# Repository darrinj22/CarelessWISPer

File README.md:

# CarelessWISPer 
Wireless Electronic Shopping Label | 
NCSU Senior Capstone Project 2021

## Introduction
CarelessWISPer, named after the famous (infamous?) George Michael song, is an Electronic Shopping Label System. Engineered
to act as an RFID area reader for consumer products, item tracking, and further applications. Using an ePaper Display, and ESP32 microcontroller, and an RFID module, this product has the capability of giving detailed item descriptions of each product on a shelf. 

## How to Browse

- This github repository is split into 3 main sections: Code, Tutorials, and Fabrication Files
- Within the code section, all of the code that was used to make this project work can be found. Note that this requires the installation of either the Arduino IDE (if you use all the code packed into one .ino file), or the Platform.io extension in Visual Studio to utilize the better and more structured codebase.
- The tutorial section contains descriptions on setting up the database using XAMPP, as well as establishing connection between the ESP32 and ePaper Display. 
- The fabrication section will contain all of the gerber files necessary to fabricate the PCB and needed parts for the project. 

## Installation
To use these code files to implement this system. Read the files contained within the Tutorials section. 

## Contact
Contact darrinjhansen@gmail.com for any questions.

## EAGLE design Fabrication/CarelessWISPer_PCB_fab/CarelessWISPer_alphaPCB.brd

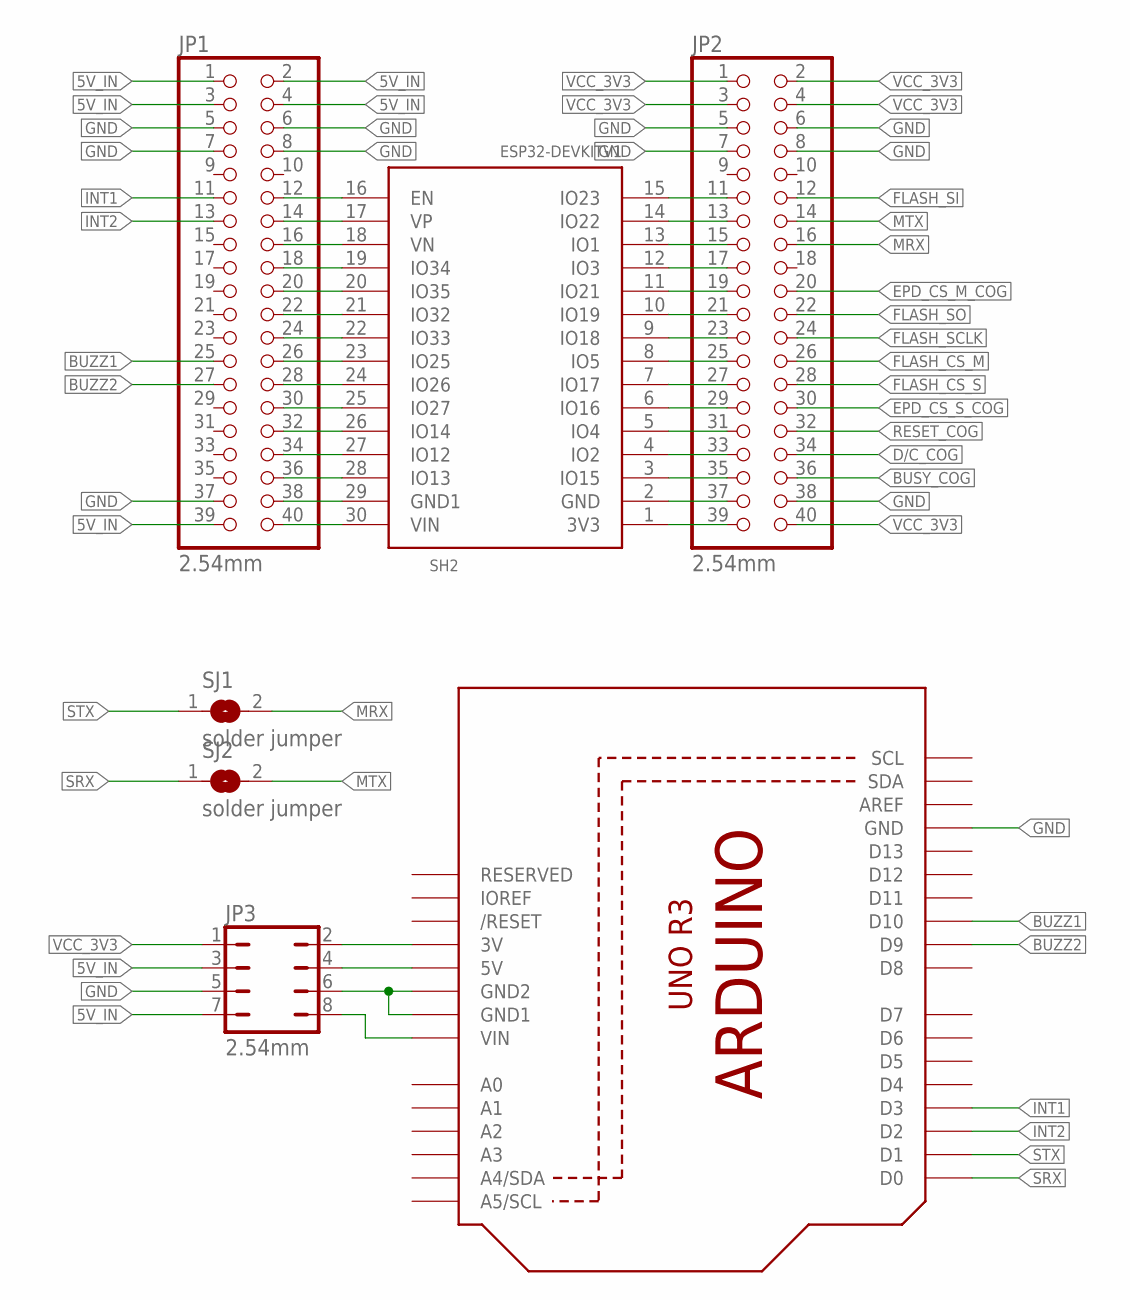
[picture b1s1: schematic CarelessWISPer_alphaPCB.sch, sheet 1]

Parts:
JP1, JP2: 2.54mm; 2X20
JP3: 2.54mm; JP4Q
SH1: ARDUINOR3-BPLACE
SH2: ESP32-DEVKIT1_FIX; ESP32-DEVKITV1
SJ1, SJ2: solder jumper; SJ

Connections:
3V: JP3.2, SH1.3V
5V: JP3.4, SH1.5V
5V_IN: JP1.1, JP1.2, JP1.3, JP1.4, JP1.39, JP3.3, JP3.7
BUSY_COG: JP2.36; also elsewhere on the board
BUZZ1: JP1.25, SH1.D10
BUZZ2: JP1.27, SH1.D9
D/C_COG: JP2.34; also elsewhere on the board
EPD_CS_M_COG: JP2.20; also elsewhere on the board
EPD_CS_S_COG: JP2.30; also elsewhere on the board
FLASH_CS_M: JP2.26; also elsewhere on the board
FLASH_CS_S: JP2.28; also elsewhere on the board
FLASH_SCLK: JP2.24; also elsewhere on the board
FLASH_SI: JP2.12; also elsewhere on the board
FLASH_SO: JP2.22; also elsewhere on the board
GND: JP1.5, JP1.6, JP1.7, JP1.8, JP1.37, JP2.5, JP2.6, JP2.7, JP2.8, JP2.38, JP3.5, SH1.GND; also elsewhere on the board
GND1: JP1.38, SH2.29 (GND1)
GND2: JP3.6, SH1.GND1, SH1.GND2
INT1: JP1.11, SH1.D3
INT2: JP1.13, SH1.D2
IO1: JP2.15, SH2.13 (IO1)
IO2: JP2.33, SH2.4 (IO2)
IO3: JP2.17, SH2.12 (IO3)
IO3V3: JP2.39, SH2.1 (3V3)
IO4: JP2.31, SH2.5 (IO4)
IO5: JP2.25, SH2.8 (IO5)
IO12: JP1.34, SH2.27 (IO12)
IO13: JP1.36, SH2.28 (IO13)
IO14: JP1.32, SH2.26 (IO14)
IO15: JP2.35, SH2.3 (IO15)
IO16: JP2.29, SH2.6 (IO16)
IO17: JP2.27, SH2.7 (IO17)
IO18: JP2.23, SH2.9 (IO18)
IO19: JP2.21, SH2.10 (IO19)
IO21: JP2.19, SH2.11 (IO21)
IO22: JP2.13, SH2.14 (IO22)
IO23: JP2.11, SH2.15 (IO23)
IO25: JP1.26, SH2.23 (IO25)
IO26: JP1.28, SH2.24 (IO26)
IO27: JP1.30, SH2.25 (IO27)
IO32: JP1.22, SH2.21 (IO32)
IO33: JP1.24, SH2.22 (IO33)
IO34: JP1.18, SH2.19 (IO34)
IO35: JP1.20, SH2.20 (IO35)
IOEN: JP1.12, SH2.16 (EN)
IOGND: JP2.37, SH2.2 (GND)
IOVIN: JP1.40, SH2.30 (VIN)
IOVN: JP1.16, SH2.18 (VN)
IOVP: JP1.14, SH2.17 (VP)
MRX: JP2.16, SJ1.2
MTX: JP2.14, SJ2.2
RESET_COG: JP2.32; also elsewhere on the board
SRX: SH1.D0, SJ2.1
STX: SH1.D1, SJ1.1
VCC_3V3: JP2.1, JP2.2, JP2.3, JP2.4, JP2.40, JP3.1; also elsewhere on the board
VIN: JP3.8, SH1.VIN

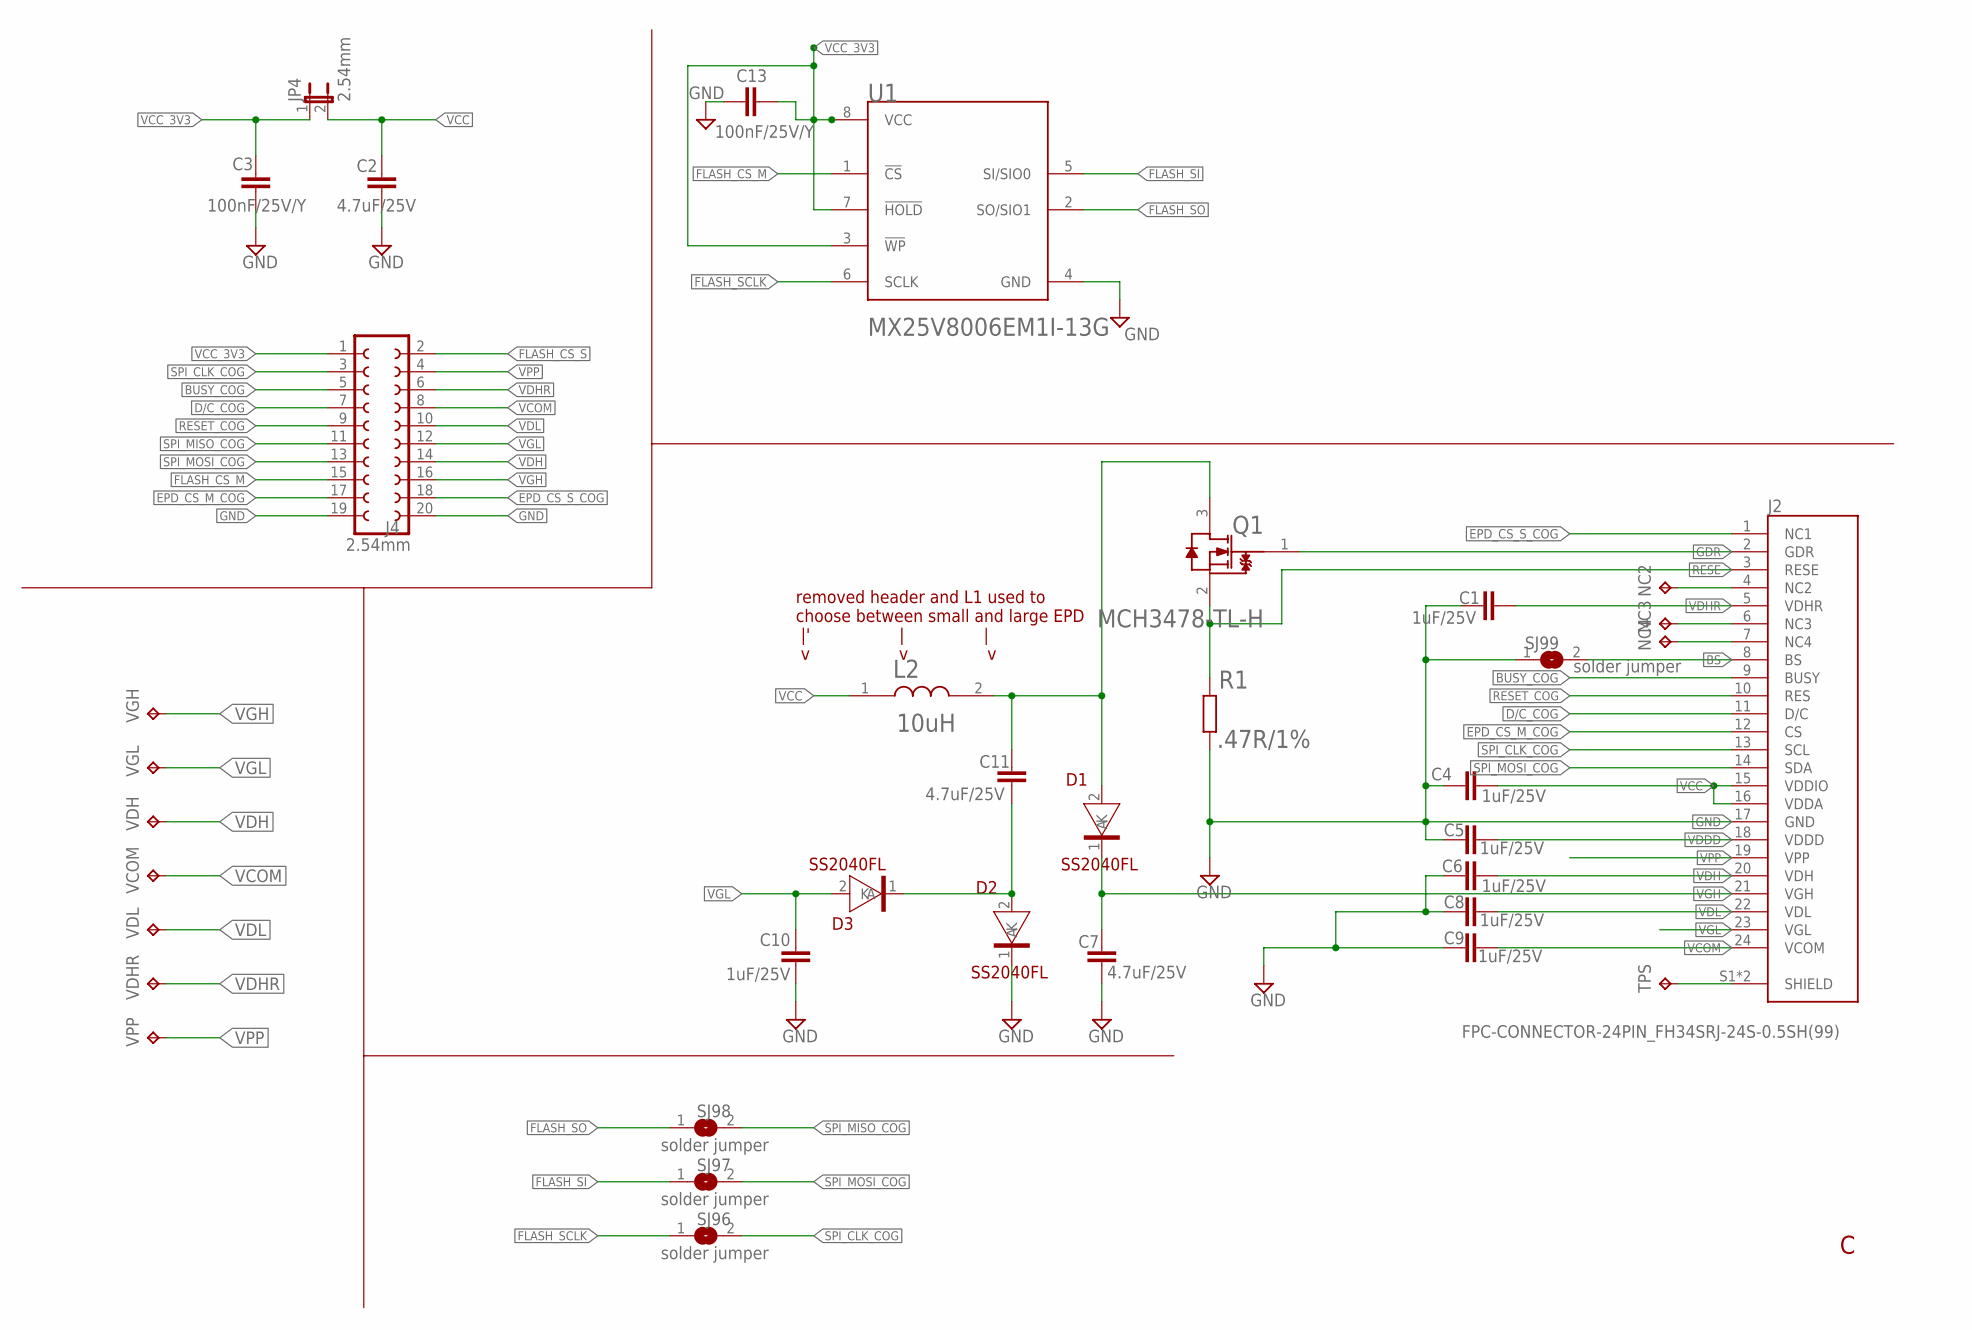
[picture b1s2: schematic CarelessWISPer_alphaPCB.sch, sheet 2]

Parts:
C1, C4, C5, C6, C8, C9, C10: 1uF/25V; CAPC2012X110
C2, C7, C11: 4.7uF/25V; CAPC2012X110
C3, C13: 100nF/25V/Y; CAPC2012X110
D1, D2, D3: SS2040FL; SOD-123FL
J2: FPC-CONNECTOR-24PIN_FH34SRJ-24S-0.5SH(99); FPC-CONNECTOR-24PIN_HRS_FH34SRJ-24S-0.5SH(99)
J4: 2.54mm; FE10-2W
JP4: 2.54mm; JP1
L2: MURATA_LQH3NPZ100MMELMURATA_LQH3NPZ100MMEL_0_0; MURATA_LQH3NPZ100MMEL_0
NC2, NC3, NC4: TPB1,27; B1,27
Q1: ON_SEMICONDUCTOR_MCH3478-TL-HON_SEMICONDUCTOR_MCH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; ON_SEMICONDUCTOR_MCH3478-TL-H_0
R1: .47R/1%; RESC2012X65
SJ96, SJ97, SJ98, SJ99: solder jumper; SJ
TPS: TPB1,27; B1,27
U1: MACRONIX_MX25V8006EM1I-13GMACRONIX_MX25V8006EM1I-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; MACRONIX_MX25V8006EM1I-13G_0
VCOM: TPB1,27; B1,27
VDH: TPB1,27; B1,27
VDHR: TPB1,27; B1,27
VDL: TPB1,27; B1,27
VGH: TPB1,27; B1,27
VGL: TPB1,27; B1,27
VPP: TPB1,27; B1,27

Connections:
BS: J2.8 (BS), SJ99.2
BUSY_COG: J2.9 (BUSY), J4.5; also elsewhere on the board
D/C_COG: J2.11 (D/C), J4.7; also elsewhere on the board
DIODE_JUNCT: C11.1, D2.2 (A), D3.1 (K)
EPD_CS_M_COG: J2.12 (CS), J4.17; also elsewhere on the board
EPD_CS_S_COG: J2.1 (NC1), J4.18; also elsewhere on the board
FLASH_CS_M: J4.15, U1.1 (!CS!); also elsewhere on the board
FLASH_CS_S: J4.2; also elsewhere on the board
FLASH_SCLK: SJ96.1, U1.6 (SCLK); also elsewhere on the board
FLASH_SI: SJ97.1, U1.5 (SI/SIO0); also elsewhere on the board
FLASH_SO: SJ98.1, U1.2 (SO/SIO1); also elsewhere on the board
GDR: J2.2 (GDR), Q1.1 (G)
GND: C1.1, C2.1, C3.1, C4.2, C5.2, C6.2, C7.1, C8.2, C9.2, C10.2, C13.1, D2.1 (K), J2.17 (GND), J4.19, J4.20, R1.1, SJ99.1, U1.4 (GND); also elsewhere on the board
L2-Q1: C11.2, D1.2 (A), L2.2, Q1.3 (D)
NC1: J2.S1 (SHIELD), J2.S2 (SHIELD), TPS.TP
NC2: J2.4 (NC2), NC2.TP
NC3: J2.6 (NC3), NC3.TP
NC4: J2.7 (NC4), NC4.TP
RESE: J2.3 (RESE), Q1.2 (S), R1.2
RESET_COG: J2.10 (RES), J4.9; also elsewhere on the board
SPI_CLK_COG: J2.13 (SCL), J4.3, SJ96.2
SPI_MISO_COG: J4.11, SJ98.2
SPI_MOSI_COG: J2.14 (SDA), J4.13, SJ97.2
VCC: C2.2, C4.1, J2.15 (VDDIO), J2.16 (VDDA), JP4.2, L2.1
VCC_3V3: C3.2, C13.2, J4.1, JP4.1, U1.3 (!WP!), U1.7 (!HOLD!), U1.8 (VCC); also elsewhere on the board
VCOM: C9.1, J2.24 (VCOM), J4.8, VCOM.TP
VDDD: C5.1, J2.18 (VDDD)
VDH: C6.1, J2.20 (VDH), J4.14, VDH.TP
VDHR: C1.2, J2.5 (VDHR), J4.6, VDHR.TP
VDL: C8.1, J2.22 (VDL), J4.10, VDL.TP
VGH: C7.2, D1.1 (K), J2.21 (VGH), J4.16, VGH.TP
VGL: C10.1, D3.2 (A), J2.23 (VGL), J4.12, VGL.TP
VPP: J2.19 (VPP), J4.4, VPP.TP

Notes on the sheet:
removed header and L1 used to choose between small and large EPD |' | | v v v

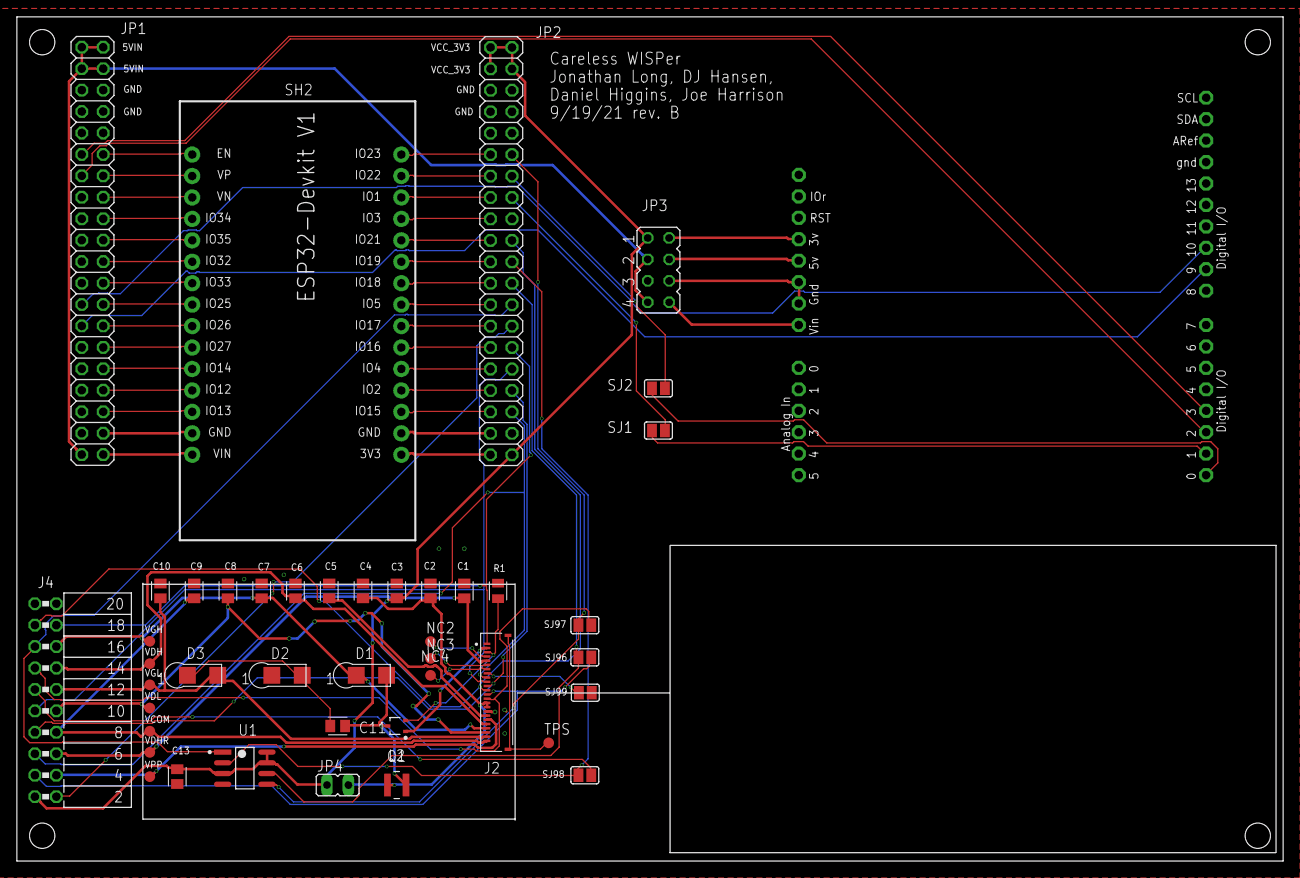
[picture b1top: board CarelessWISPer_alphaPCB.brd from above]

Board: 2 copper layers, 150.0 x 100.0 mm, 44 parts (0 on the bottom side), 76 nets.

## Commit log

2021-11-28 Create create_procedure_mysql
    Function that is called by php file
2021-11-30 Create stuff
2021-11-30 Create CarelessWISPer_PCB_fab
2022-06-07 Organizing Content
2022-06-07 Organization Changes
